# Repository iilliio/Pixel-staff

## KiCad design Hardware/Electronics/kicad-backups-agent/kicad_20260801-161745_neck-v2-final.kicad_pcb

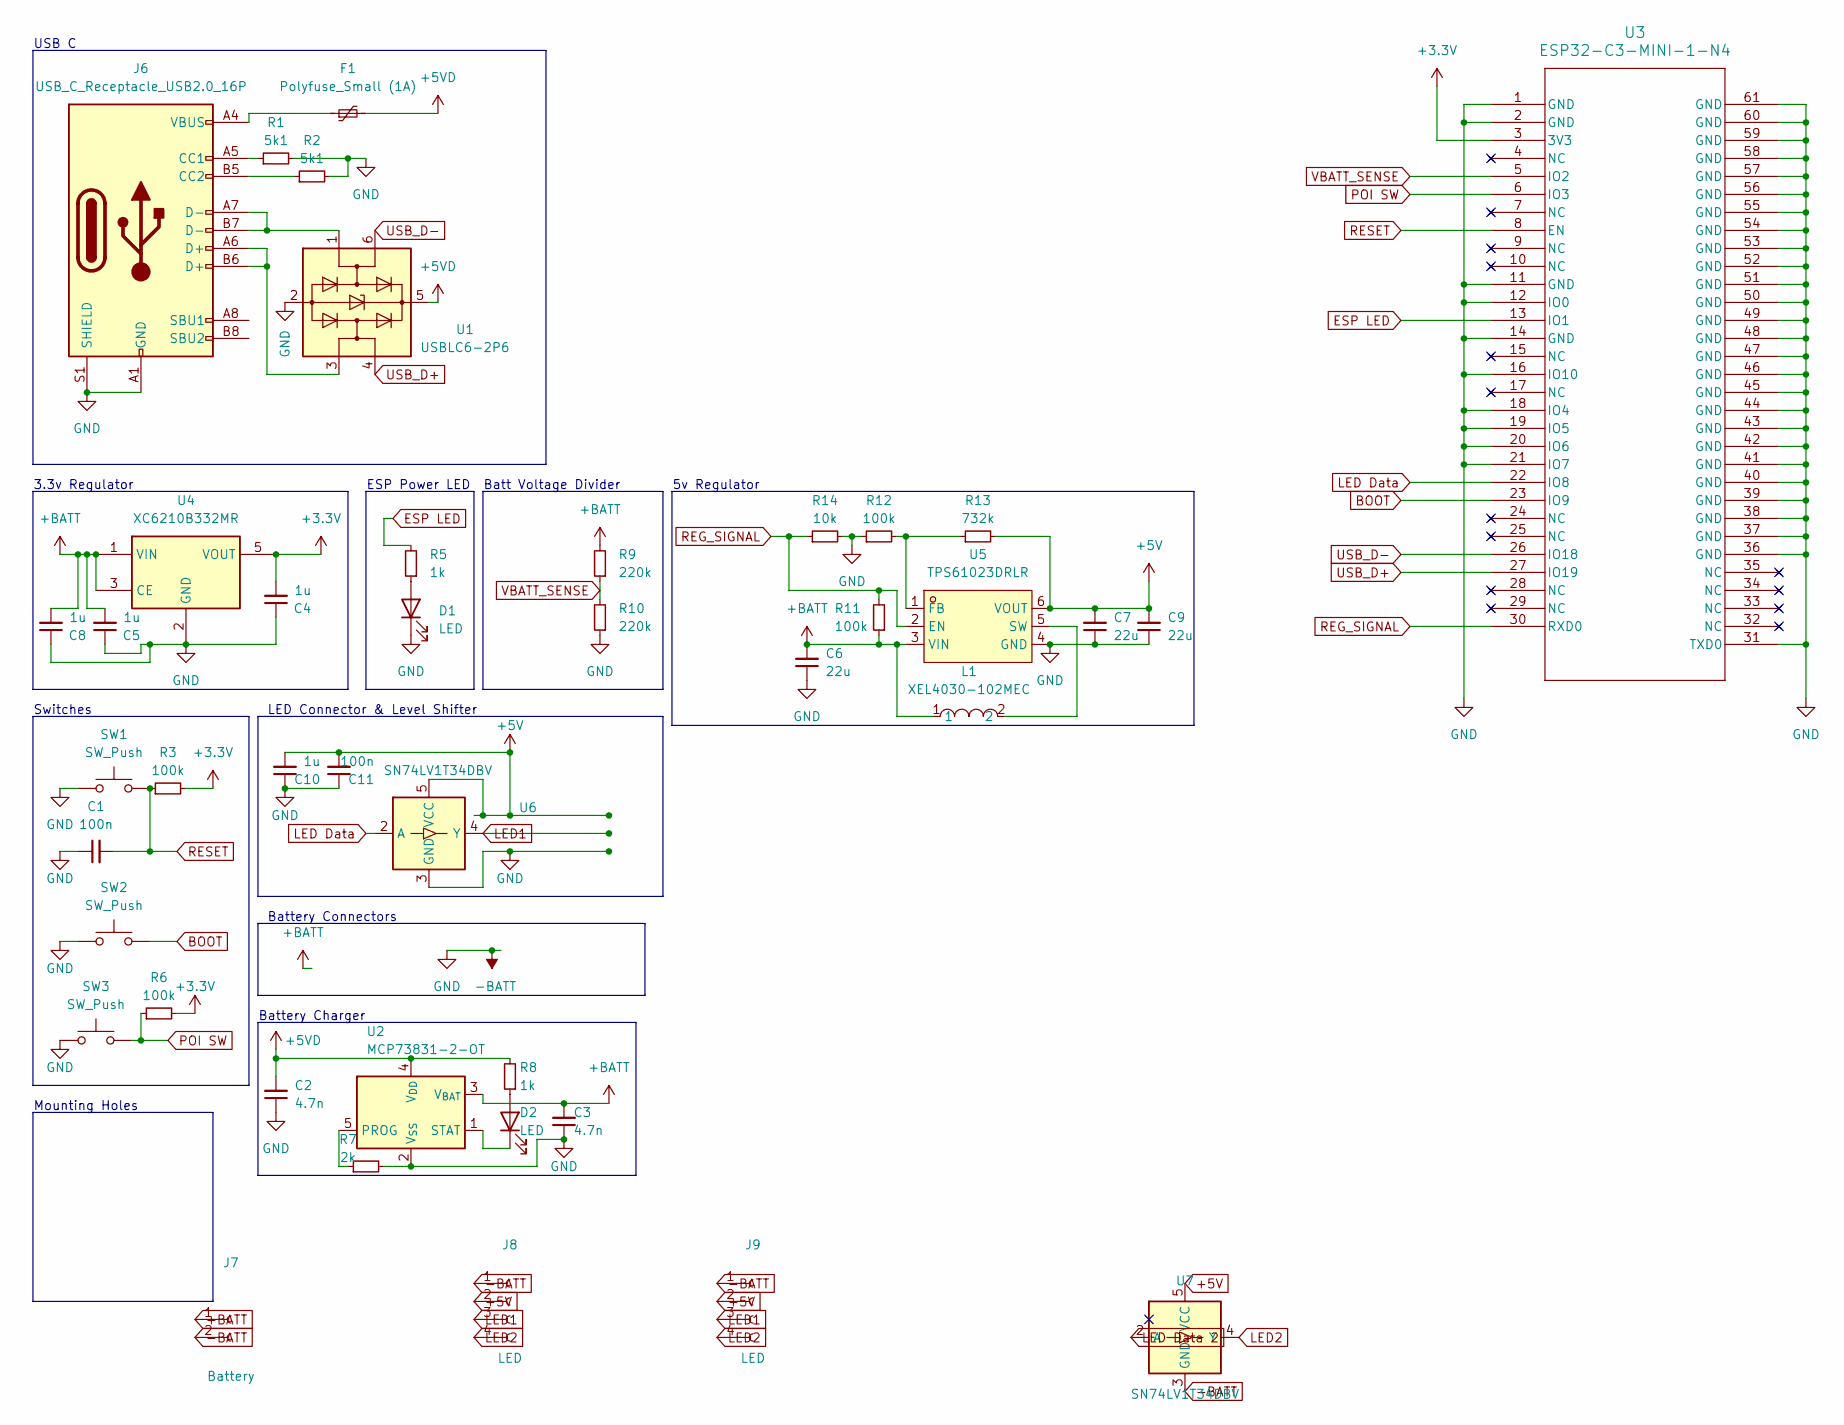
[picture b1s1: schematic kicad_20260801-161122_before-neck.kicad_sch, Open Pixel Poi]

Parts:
C1, C11: 100n; C_0805_2012Metric; LCSC C83055
C2, C3: 4.7n; C_0805_2012Metric; LCSC C123621
C4, C5, C8, C10: 1u; C_0805_2012Metric; LCSC C28323
C6, C7, C9: 22u; C_0805_2012Metric; LCSC C45783
D1, D2: LED; LED_0603_1608Metric; LCSC C965807
F1: Polyfuse_Small (1A); Fuse_1206_3216Metric; LCSC C720075
J6: USB_C_Receptacle_USB2.0_16P; USB_C_Receptacle_HRO_TYPE-C-31-M-12; LCSC C2765186
J7: Battery; JST_PH_B2B-PH-K_1x02_P2.00mm_Vertical
J8, J9: LED; JST_GH_BM04B-GHS-TBT_1x04-1MP_P1.25mm_Vertical
L1: XEL4030-102MEC; IND-SMD_L4.0-W4.0-A; LCSC Part C5441341
R1, R2: 5k1; R_0603_1608Metric; LCSC C14677
R3, R6, R11, R12: 100k; R_0603_1608Metric; LCSC C14675
R5, R8: 1k; R_0603_1608Metric; LCSC C22548
R7: 2k; R_0603_1608Metric; LCSC C22975
R9, R10: 220k; R_0603_1608Metric; LCSC C22961
R13: 732k; R_0603_1608Metric; LCSC C246003
R14: 10k; R_0603_1608Metric; LCSC C98220
SW1, SW2: SW_Push; SW_SPST_B3U-1000P; LCSC C231329
SW3: SW_Push; Panasonic_EVQPUL_EVQPUC; LCSC C397351
U1: USBLC6-2P6; SOT-666; LCSC C15999
U2: MCP73831-2-OT; SOT-23-5; LCSC C424093
U3: ESP32-C3-MINI-1-N4; ESP32-C3-MINI-1_EXP; LCSC C2934569
U4: XC6210B332MR; SOT-23-5; LCSC C47719
U5: TPS61023DRLR; SOT-563_L1.6-W1.2-P0.50-LS1.6-BR; LCSC Part C919459
U6: SN74LV1T34DBV; SOT-23-5; LCSC C100024
U7: SN74LV1T34DBV; SOT-23-5

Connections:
+3.3V: C4.2, R3.2, R6.2, U3.3 (3V3), U4.5 (VOUT)
+5V: C7.2, C9.2, C10.2, C11.2, J8.2, J9.2, R13.2, U5.6 (VOUT), U6.5 (VCC), U7.5 (VCC)
+5VD: C2.2, F1.2, R8.2, U1.5 (VBUS), U2.4 (V_{DD})
+BATT: C3.2, C5.2, C6.2, C8.2, J7.1, L1.1, R9.2, R11.1, U2.3 (V_{BAT}), U4.1 (VIN), U4.3 (CE), U5.3 (VIN)
-BATT: C1.1, C2.1, C3.1, C4.1, C5.1, C6.1, C7.1, C8.1, C9.1, C10.1, C11.1, D1.1 (K), J6.A1 (GND), J6.A12 (GND), J6.B1 (GND), J6.B12 (GND), J6.S1 (SHIELD), J7.2, J8.1, J9.1, R1.2, R2.2, R7.2, R10.1, R12.1, R14.2, SW1.1, SW2.1, SW3.1, U1.2 (GND), U2.2 (V_{SS}), U3.1 (GND), U3.2 (GND), U3.11 (GND), U3.12 (IO0), U3.14 (GND), U3.16 (IO10), U3.18 (IO4), U3.19 (IO5), U3.20 (IO6), U3.21 (IO7), U3.31 (TXD0), U3.36 (GND), U3.37 (GND), U3.38 (GND), U3.39 (GND), U3.40 (GND), U3.41 (GND), U3.42 (GND), U3.43 (GND), U3.44 (GND), U3.45 (GND), U3.46 (GND), U3.47 (GND), U3.48 (GND), U3.49 (GND), U3.50 (GND), U3.51 (GND), U3.52 (GND), U3.53 (GND), U3.54 (GND), U3.55 (GND), U3.56 (GND), U3.57 (GND), U3.58 (GND), U3.59 (GND), U3.60 (GND), U3.61 (GND), U4.2 (GND), U5.4 (GND), U6.3 (GND), U7.3 (GND)
BOOT: SW2.2, U3.23 (IO9)
ESP LED: R5.2, U3.13 (IO1)
LED1: J8.3, J9.3, U6.4 (Y)
LED2: J8.4, J9.4, U7.4 (Y)
LED Data: U3.22 (IO8), U6.2 (A)
LED Data 2: U7.2 (A)
unnamed: D1.2 (A), R5.1
unnamed: D2.2 (A), R8.1
unnamed: D2.1 (K), U2.1 (STAT)
unnamed: F1.1, J6.A4 (VBUS), J6.A9 (VBUS), J6.B4 (VBUS), J6.B9 (VBUS)
unnamed: J6.A5 (CC1), R1.1
unnamed: J6.B5 (CC2), R2.1
unnamed: J6.A6 (D+), J6.B6 (D+), U1.3 (I/O2)
unnamed: J6.A7 (D-), J6.B7 (D-), U1.1 (I/O1)
unnamed: R7.1, U2.5 (PROG)
unnamed: R12.2, R13.1, U5.1 (FB)
unnamed: L1.2, U5.5 (SW)
POI SW: R6.1, SW3.2, U3.6 (IO3); also elsewhere on the board
REG_SIGNAL: R11.2, R14.1, U3.30 (RXD0), U5.2 (EN)
RESET: C1.2, R3.1, SW1.2, U3.8 (EN)
USB_D+: U1.4 (I/O2), U3.27 (IO19)
USB_D-: U1.6 (I/O1), U3.26 (IO18)
VBATT_SENSE: R9.1, R10.2, U3.5 (IO2)

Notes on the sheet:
Battery Connectors
Batt Voltage Divider
Mounting Holes
LED Connector & Level Shifter
USB C
5v Regulator
3.3v Regulator
ESP Power LED
Switches
Battery Charger

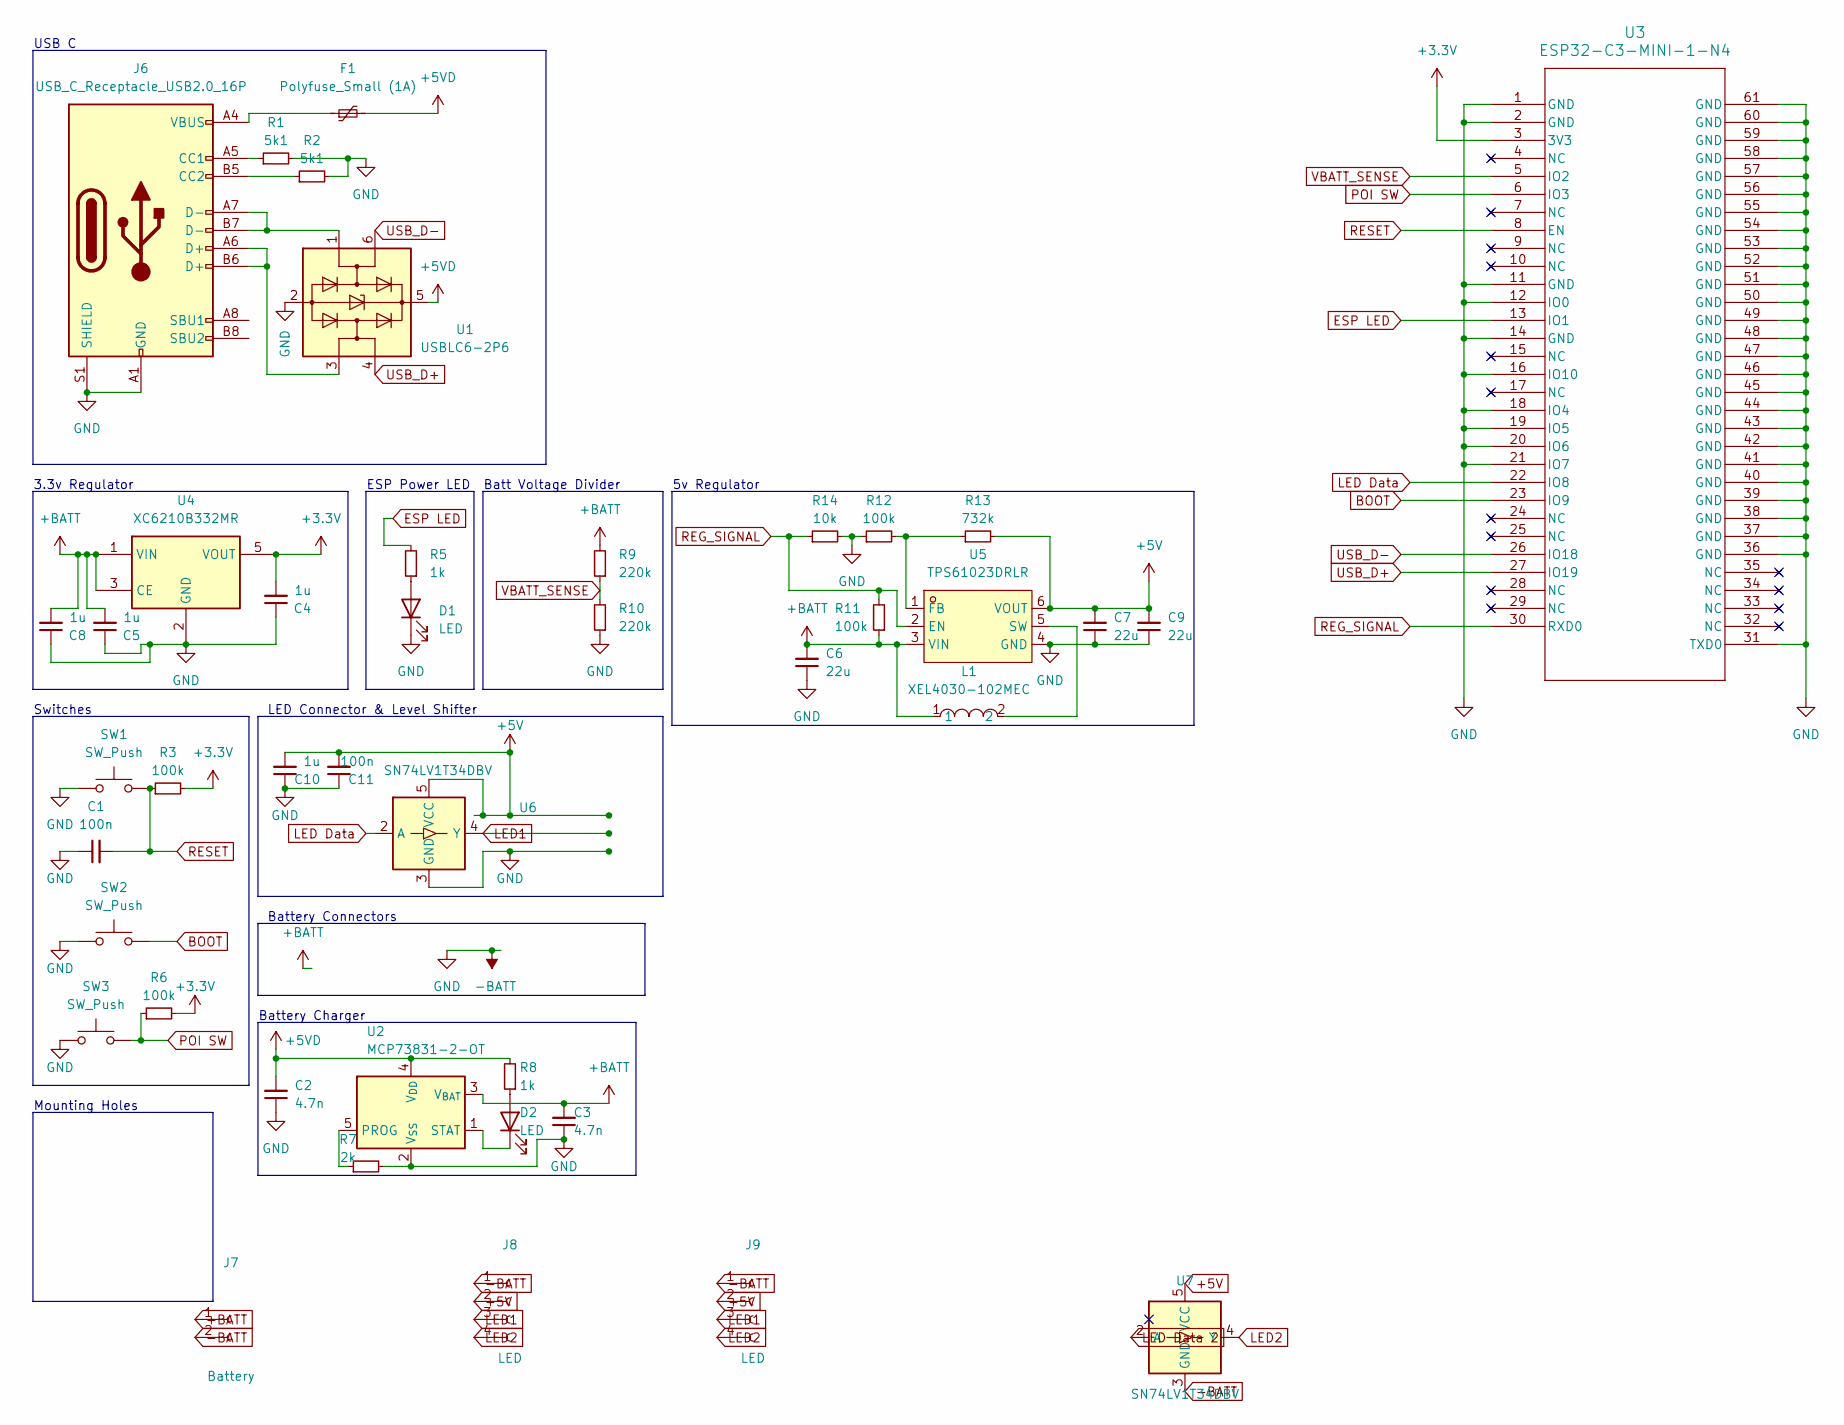
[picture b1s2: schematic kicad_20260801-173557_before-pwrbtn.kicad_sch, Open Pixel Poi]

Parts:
C1, C11: 100n; C_0805_2012Metric; LCSC C83055
C2, C3: 4.7n; C_0805_2012Metric; LCSC C123621
C4, C5, C8, C10: 1u; C_0805_2012Metric; LCSC C28323
C6, C7, C9: 22u; C_0805_2012Metric; LCSC C45783
D1, D2: LED; LED_0603_1608Metric; LCSC C965807
F1: Polyfuse_Small (1A); Fuse_1206_3216Metric; LCSC C720075
J6: USB_C_Receptacle_USB2.0_16P; USB_C_Receptacle_HRO_TYPE-C-31-M-12; LCSC C2765186
J7: Battery; JST_PH_B2B-PH-K_1x02_P2.00mm_Vertical
J8, J9: LED; LED_Strip_SolderPads_1x04
L1: XEL4030-102MEC; IND-SMD_L4.0-W4.0-A; LCSC Part C5441341
R1, R2: 5k1; R_0603_1608Metric; LCSC C14677
R3, R6, R11, R12: 100k; R_0603_1608Metric; LCSC C14675
R5, R8: 1k; R_0603_1608Metric; LCSC C22548
R7: 2k; R_0603_1608Metric; LCSC C22975
R9, R10: 220k; R_0603_1608Metric; LCSC C22961
R13: 732k; R_0603_1608Metric; LCSC C246003
R14: 10k; R_0603_1608Metric; LCSC C98220
SW1, SW2: SW_Push; SW_SPST_B3U-1000P; LCSC C231329
SW3: SW_Push; Panasonic_EVQPUL_EVQPUC; LCSC C397351
U1: USBLC6-2P6; SOT-666; LCSC C15999
U2: MCP73831-2-OT; SOT-23-5; LCSC C424093
U3: ESP32-C3-MINI-1-N4; ESP32-C3-MINI-1_EXP; LCSC C2934569
U4: XC6210B332MR; SOT-23-5; LCSC C47719
U5: TPS61023DRLR; SOT-563_L1.6-W1.2-P0.50-LS1.6-BR; LCSC Part C919459
U6: SN74LV1T34DBV; SOT-23-5; LCSC C100024
U7: SN74LV1T34DBV; SOT-23-5

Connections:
+3.3V: C4.2, R3.2, R6.2, U3.3 (3V3), U4.5 (VOUT)
+5V: C7.2, C9.2, C10.2, C11.2, J8.2, J9.2, R13.2, U5.6 (VOUT), U6.5 (VCC), U7.5 (VCC)
+5VD: C2.2, F1.2, R8.2, U1.5 (VBUS), U2.4 (V_{DD})
+BATT: C3.2, C5.2, C6.2, C8.2, J7.1, L1.1, R9.2, R11.1, U2.3 (V_{BAT}), U4.1 (VIN), U4.3 (CE), U5.3 (VIN)
-BATT: C1.1, C2.1, C3.1, C4.1, C5.1, C6.1, C7.1, C8.1, C9.1, C10.1, C11.1, D1.1 (K), J6.A1 (GND), J6.A12 (GND), J6.B1 (GND), J6.B12 (GND), J6.S1 (SHIELD), J7.2, J8.1, J9.1, R1.2, R2.2, R7.2, R10.1, R12.1, R14.2, SW1.1, SW2.1, SW3.1, U1.2 (GND), U2.2 (V_{SS}), U3.1 (GND), U3.2 (GND), U3.11 (GND), U3.12 (IO0), U3.14 (GND), U3.16 (IO10), U3.18 (IO4), U3.19 (IO5), U3.20 (IO6), U3.21 (IO7), U3.31 (TXD0), U3.36 (GND), U3.37 (GND), U3.38 (GND), U3.39 (GND), U3.40 (GND), U3.41 (GND), U3.42 (GND), U3.43 (GND), U3.44 (GND), U3.45 (GND), U3.46 (GND), U3.47 (GND), U3.48 (GND), U3.49 (GND), U3.50 (GND), U3.51 (GND), U3.52 (GND), U3.53 (GND), U3.54 (GND), U3.55 (GND), U3.56 (GND), U3.57 (GND), U3.58 (GND), U3.59 (GND), U3.60 (GND), U3.61 (GND), U4.2 (GND), U5.4 (GND), U6.3 (GND), U7.3 (GND)
BOOT: SW2.2, U3.23 (IO9)
ESP LED: R5.2, U3.13 (IO1)
LED1: J8.3, J9.3, U6.4 (Y)
LED2: J8.4, J9.4, U7.4 (Y)
LED Data: U3.22 (IO8), U6.2 (A)
LED Data 2: U7.2 (A)
unnamed: D1.2 (A), R5.1
unnamed: D2.2 (A), R8.1
unnamed: D2.1 (K), U2.1 (STAT)
unnamed: F1.1, J6.A4 (VBUS), J6.A9 (VBUS), J6.B4 (VBUS), J6.B9 (VBUS)
unnamed: J6.A5 (CC1), R1.1
unnamed: J6.B5 (CC2), R2.1
unnamed: J6.A6 (D+), J6.B6 (D+), U1.3 (I/O2)
unnamed: J6.A7 (D-), J6.B7 (D-), U1.1 (I/O1)
unnamed: R7.1, U2.5 (PROG)
unnamed: R12.2, R13.1, U5.1 (FB)
unnamed: L1.2, U5.5 (SW)
POI SW: R6.1, SW3.2, U3.6 (IO3); also elsewhere on the board
REG_SIGNAL: R11.2, R14.1, U3.30 (RXD0), U5.2 (EN)
RESET: C1.2, R3.1, SW1.2, U3.8 (EN)
USB_D+: U1.4 (I/O2), U3.27 (IO19)
USB_D-: U1.6 (I/O1), U3.26 (IO18)
VBATT_SENSE: R9.1, R10.2, U3.5 (IO2)

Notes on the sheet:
Battery Connectors
Batt Voltage Divider
Mounting Holes
LED Connector & Level Shifter
USB C
5v Regulator
3.3v Regulator
ESP Power LED
Switches
Battery Charger

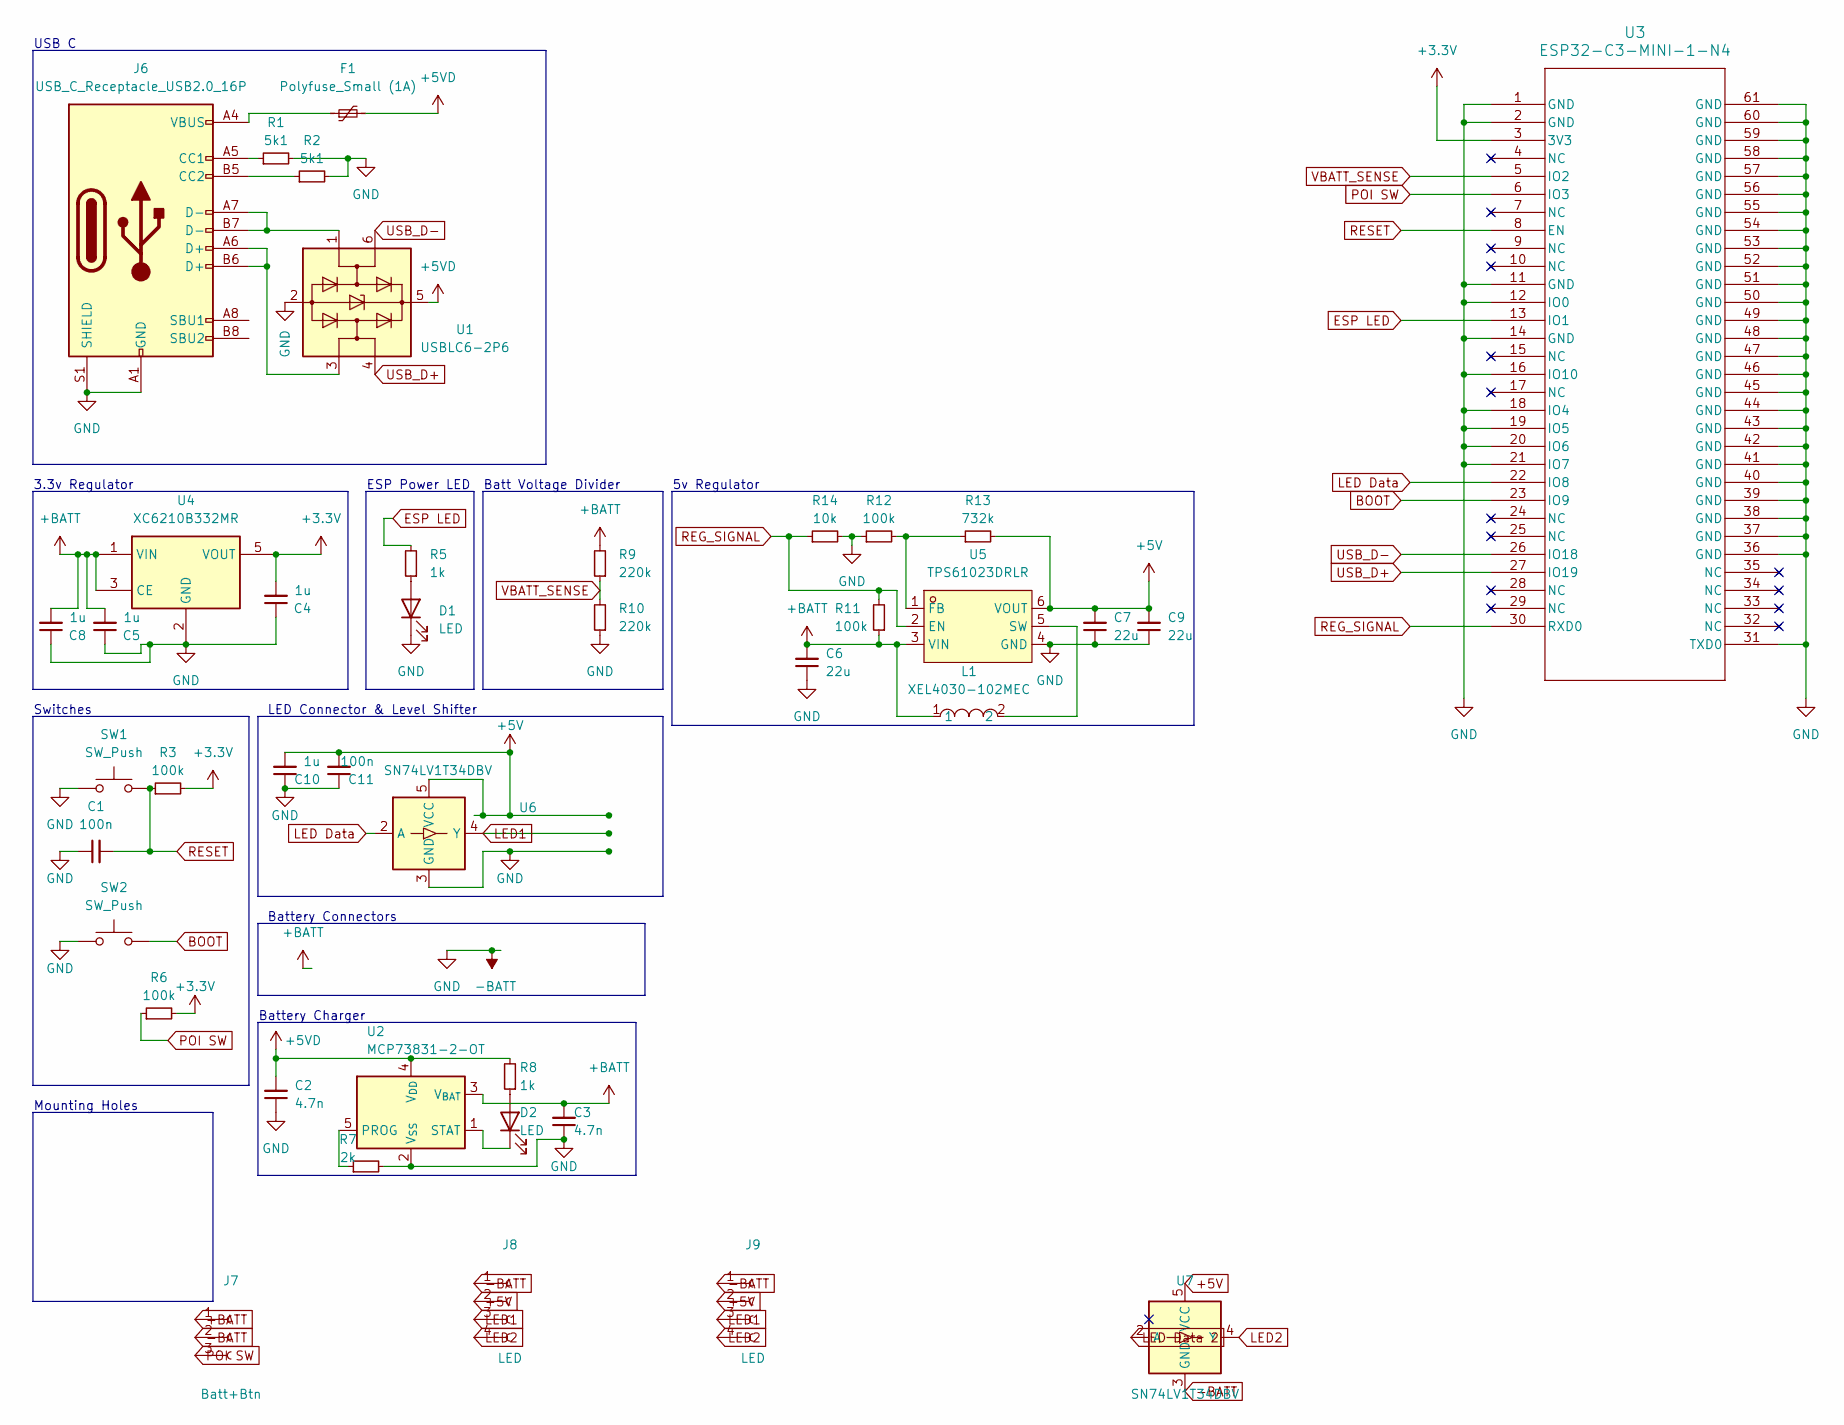
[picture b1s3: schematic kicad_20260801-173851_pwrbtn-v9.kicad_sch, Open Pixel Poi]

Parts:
C1, C11: 100n; C_0805_2012Metric; LCSC C83055
C2, C3: 4.7n; C_0805_2012Metric; LCSC C123621
C4, C5, C8, C10: 1u; C_0805_2012Metric; LCSC C28323
C6, C7, C9: 22u; C_0805_2012Metric; LCSC C45783
D1, D2: LED; LED_0603_1608Metric; LCSC C965807
F1: Polyfuse_Small (1A); Fuse_1206_3216Metric; LCSC C720075
J6: USB_C_Receptacle_USB2.0_16P; USB_C_Receptacle_HRO_TYPE-C-31-M-12; LCSC C2765186
J7: Batt+Btn; Power_Button_SolderPads_1x03
J8, J9: LED; LED_Strip_SolderPads_1x04
L1: XEL4030-102MEC; IND-SMD_L4.0-W4.0-A; LCSC Part C5441341
R1, R2: 5k1; R_0603_1608Metric; LCSC C14677
R3, R6, R11, R12: 100k; R_0603_1608Metric; LCSC C14675
R5, R8: 1k; R_0603_1608Metric; LCSC C22548
R7: 2k; R_0603_1608Metric; LCSC C22975
R9, R10: 220k; R_0603_1608Metric; LCSC C22961
R13: 732k; R_0603_1608Metric; LCSC C246003
R14: 10k; R_0603_1608Metric; LCSC C98220
SW1, SW2: SW_Push; SW_SPST_B3U-1000P; LCSC C231329
U1: USBLC6-2P6; SOT-666; LCSC C15999
U2: MCP73831-2-OT; SOT-23-5; LCSC C424093
U3: ESP32-C3-MINI-1-N4; ESP32-C3-MINI-1_EXP; LCSC C2934569
U4: XC6210B332MR; SOT-23-5; LCSC C47719
U5: TPS61023DRLR; SOT-563_L1.6-W1.2-P0.50-LS1.6-BR; LCSC Part C919459
U6: SN74LV1T34DBV; SOT-23-5; LCSC C100024
U7: SN74LV1T34DBV; SOT-23-5

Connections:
+3.3V: C4.2, R3.2, R6.2, U3.3 (3V3), U4.5 (VOUT)
+5V: C7.2, C9.2, C10.2, C11.2, J8.2, J9.2, R13.2, U5.6 (VOUT), U6.5 (VCC), U7.5 (VCC)
+5VD: C2.2, F1.2, R8.2, U1.5 (VBUS), U2.4 (V_{DD})
+BATT: C3.2, C5.2, C6.2, C8.2, J7.1, L1.1, R9.2, R11.1, U2.3 (V_{BAT}), U4.1 (VIN), U4.3 (CE), U5.3 (VIN)
-BATT: C1.1, C2.1, C3.1, C4.1, C5.1, C6.1, C7.1, C8.1, C9.1, C10.1, C11.1, D1.1 (K), J6.A1 (GND), J6.A12 (GND), J6.B1 (GND), J6.B12 (GND), J6.S1 (SHIELD), J7.2, J8.1, J9.1, R1.2, R2.2, R7.2, R10.1, R12.1, R14.2, SW1.1, SW2.1, U1.2 (GND), U2.2 (V_{SS}), U3.1 (GND), U3.2 (GND), U3.11 (GND), U3.12 (IO0), U3.14 (GND), U3.16 (IO10), U3.18 (IO4), U3.19 (IO5), U3.20 (IO6), U3.21 (IO7), U3.31 (TXD0), U3.36 (GND), U3.37 (GND), U3.38 (GND), U3.39 (GND), U3.40 (GND), U3.41 (GND), U3.42 (GND), U3.43 (GND), U3.44 (GND), U3.45 (GND), U3.46 (GND), U3.47 (GND), U3.48 (GND), U3.49 (GND), U3.50 (GND), U3.51 (GND), U3.52 (GND), U3.53 (GND), U3.54 (GND), U3.55 (GND), U3.56 (GND), U3.57 (GND), U3.58 (GND), U3.59 (GND), U3.60 (GND), U3.61 (GND), U4.2 (GND), U5.4 (GND), U6.3 (GND), U7.3 (GND); also elsewhere on the board
BOOT: SW2.2, U3.23 (IO9)
ESP LED: R5.2, U3.13 (IO1)
LED1: J8.3, J9.3, U6.4 (Y)
LED2: J8.4, J9.4, U7.4 (Y)
LED Data: U3.22 (IO8), U6.2 (A)
LED Data 2: U7.2 (A)
unnamed: D1.2 (A), R5.1
unnamed: D2.2 (A), R8.1
unnamed: D2.1 (K), U2.1 (STAT)
unnamed: F1.1, J6.A4 (VBUS), J6.A9 (VBUS), J6.B4 (VBUS), J6.B9 (VBUS)
unnamed: J6.A5 (CC1), R1.1
unnamed: J6.B5 (CC2), R2.1
unnamed: J6.A6 (D+), J6.B6 (D+), U1.3 (I/O2)
unnamed: J6.A7 (D-), J6.B7 (D-), U1.1 (I/O1)
unnamed: R7.1, U2.5 (PROG)
unnamed: R12.2, R13.1, U5.1 (FB)
unnamed: L1.2, U5.5 (SW)
POI SW: J7.3, R6.1, U3.6 (IO3); also elsewhere on the board
REG_SIGNAL: R11.2, R14.1, U3.30 (RXD0), U5.2 (EN)
RESET: C1.2, R3.1, SW1.2, U3.8 (EN)
USB_D+: U1.4 (I/O2), U3.27 (IO19)
USB_D-: U1.6 (I/O1), U3.26 (IO18)
VBATT_SENSE: R9.1, R10.2, U3.5 (IO2)

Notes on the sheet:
Battery Connectors
Batt Voltage Divider
Mounting Holes
LED Connector & Level Shifter
USB C
5v Regulator
3.3v Regulator
ESP Power LED
Switches
Battery Charger

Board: 2 copper layers, 42 parts (1 on the bottom side), 27 nets, no tracks yet.
